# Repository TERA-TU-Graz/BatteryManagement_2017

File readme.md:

# Battery Management System (BMS) with use of STM32 CubeMX

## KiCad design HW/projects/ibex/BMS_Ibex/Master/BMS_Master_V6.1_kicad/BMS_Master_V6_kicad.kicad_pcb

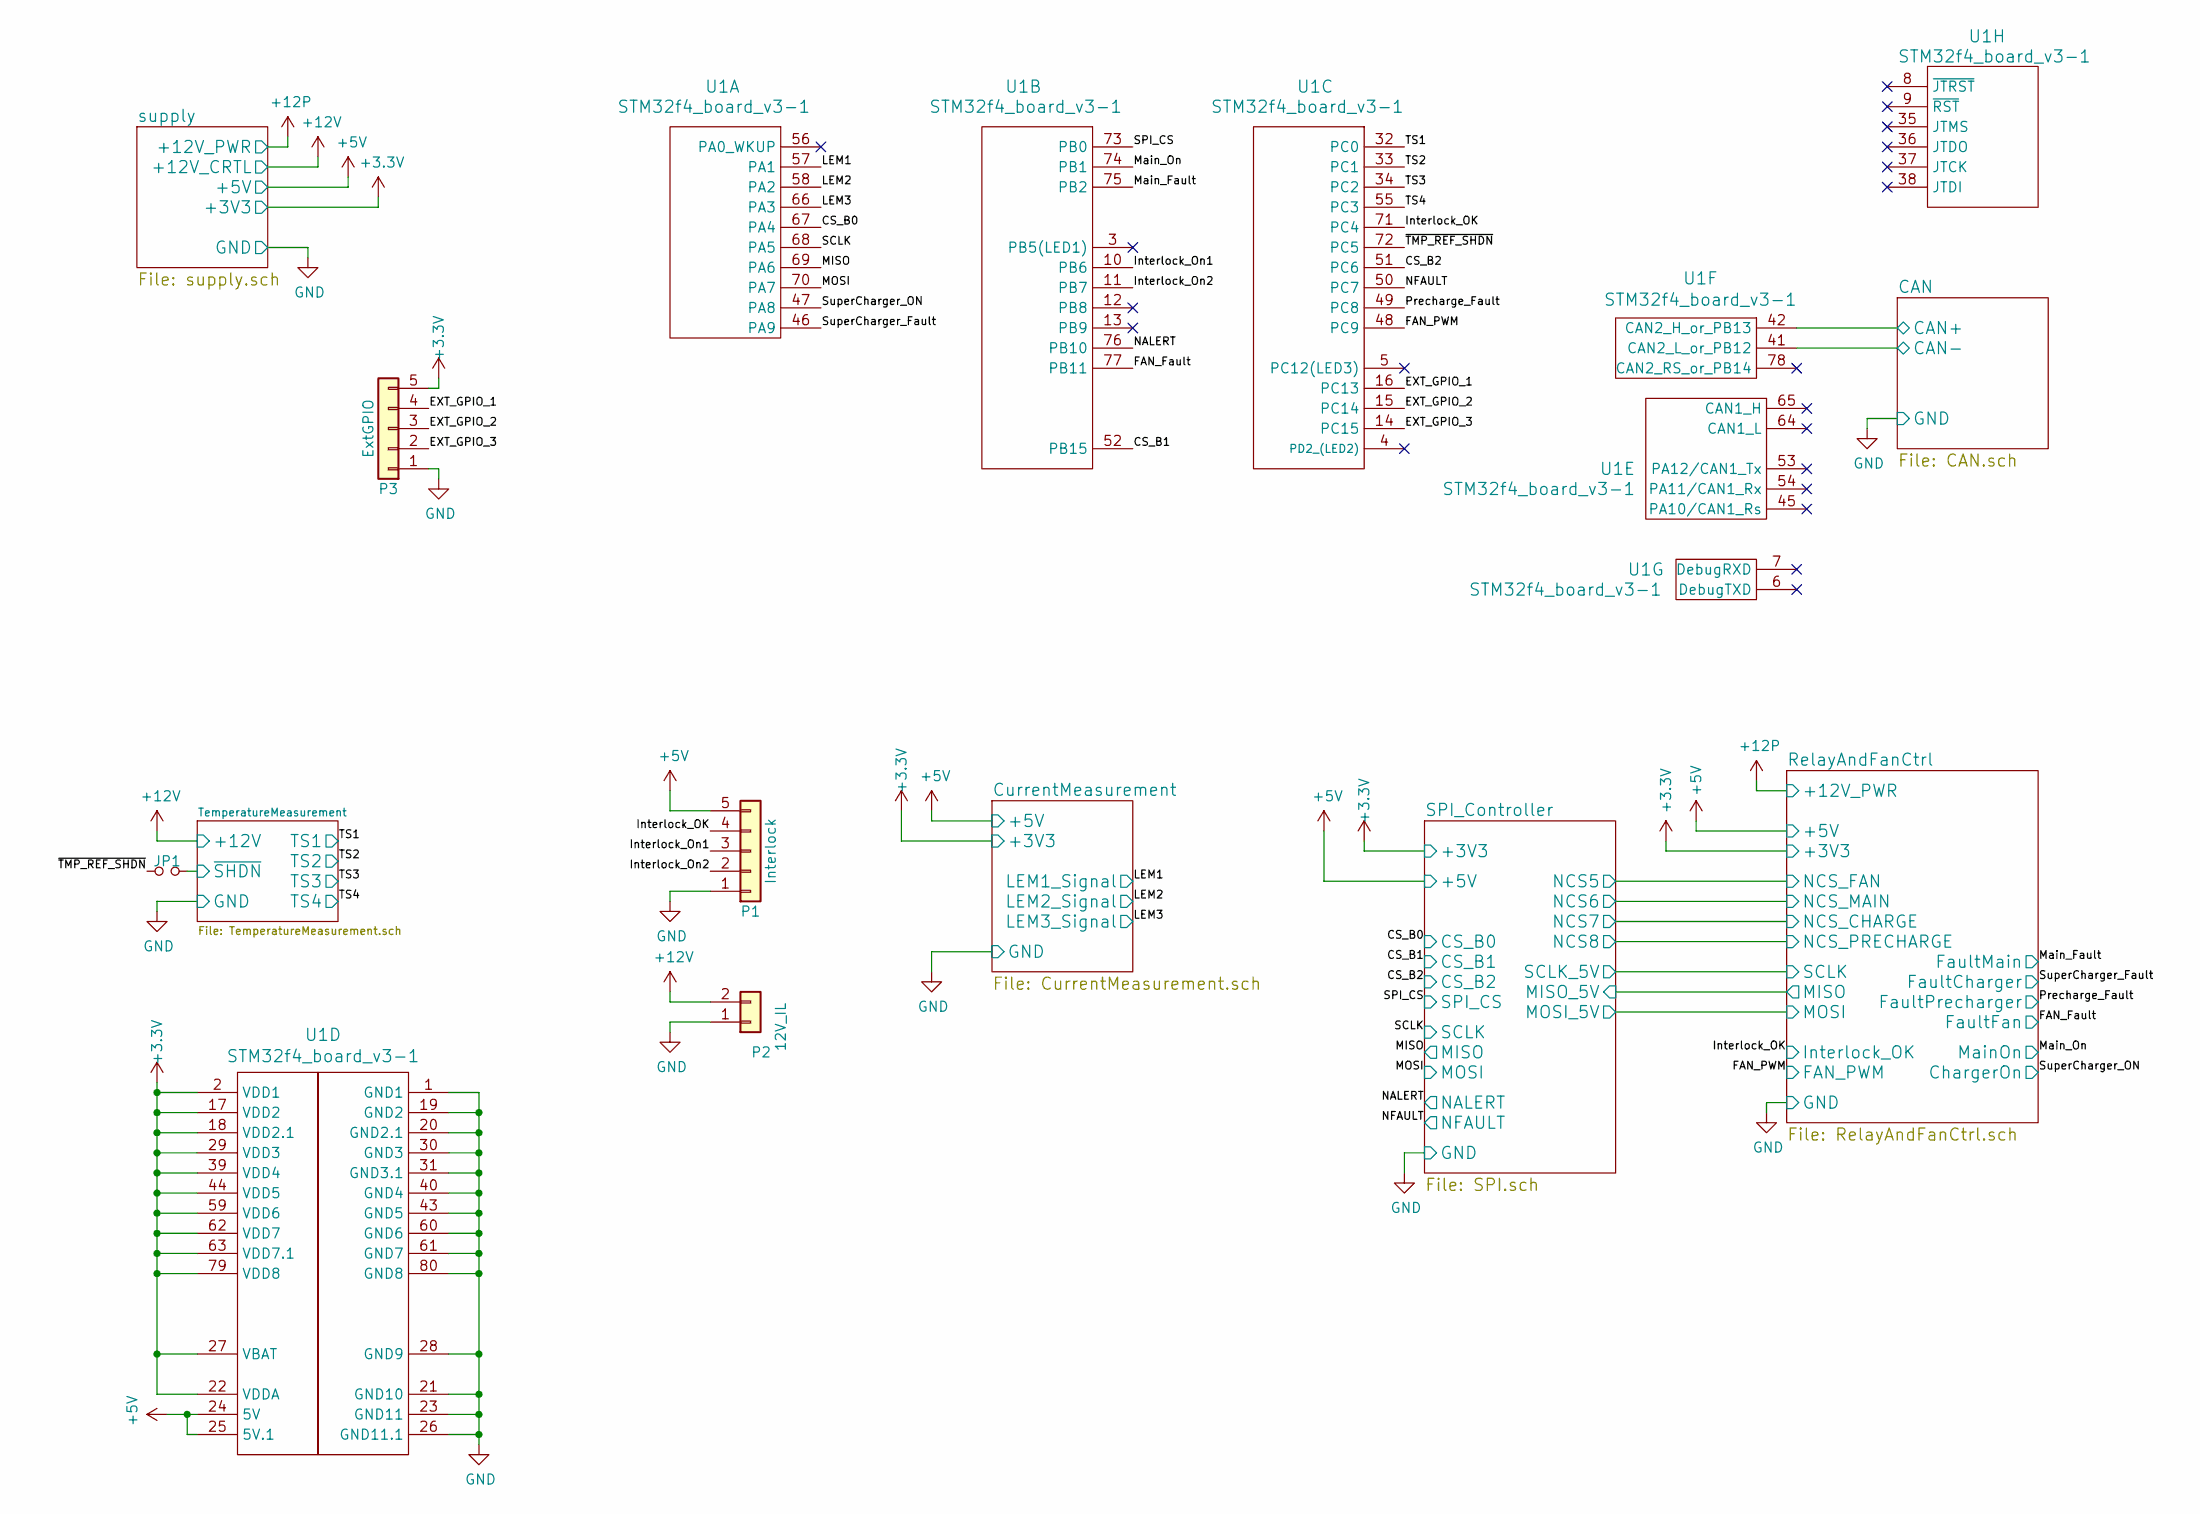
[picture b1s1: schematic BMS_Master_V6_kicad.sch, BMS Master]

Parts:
JP1: Jumper_NO_Small; SOLDERJUMPER_2
P1: Interlock; JST_XH_B05B-XH-A_05x2.50mm_Straight
P2: 12V_IL; JST_XH_B02B-XH-A_02x2.50mm_Straight
P3: ExtGPIO; JST_EH_B05B-EH-A_05x2.50mm_Straight
U1: STM32f4_board_v3-1; STM32f4-board_v3-1

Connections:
+3V3: P3.5, U1.2 (VDD1), U1.17 (VDD2), U1.18 (VDD2.1), U1.22 (VDDA), U1.27 (VBAT), U1.29 (VDD3), U1.39 (VDD4), U1.44 (VDD5), U1.59 (VDD6), U1.62 (VDD7), U1.63 (VDD7.1), U1.79 (VDD8); also elsewhere on the board
+5V: P1.5, U1.24 (5V), U1.25 (5V.1); also elsewhere on the board
+12V: P2.2; also elsewhere on the board
/CAN/CAN+: U1.42 (CAN2_H_or_PB13); also elsewhere on the board
/CAN/CAN-: U1.41 (CAN2_L_or_PB12); also elsewhere on the board
/CS_B0: U1.67 (PA4); also elsewhere on the board
/CS_B1: U1.52 (PB15); also elsewhere on the board
/CS_B2: U1.51 (PC6); also elsewhere on the board
/EXT_GPIO_1: P3.4, U1.16 (PC13)
/EXT_GPIO_2: P3.3, U1.15 (PC14)
/EXT_GPIO_3: P3.2, U1.14 (PC15)
/FAN_Fault: U1.77 (PB11); also elsewhere on the board
/FAN_PWM: U1.48 (PC9); also elsewhere on the board
/Interlock_OK: P1.4, U1.71 (PC4); also elsewhere on the board
/Interlock_On1: P1.3, U1.10 (PB6)
/Interlock_On2: P1.2, U1.11 (PB7)
/LEM1: U1.57 (PA1); also elsewhere on the board
/LEM2: U1.58 (PA2); also elsewhere on the board
/LEM3: U1.66 (PA3); also elsewhere on the board
/MISO: U1.69 (PA6); also elsewhere on the board
/MOSI: U1.70 (PA7); also elsewhere on the board
/Main_Fault: U1.75 (PB2); also elsewhere on the board
/Main_On: U1.74 (PB1); also elsewhere on the board
/NALERT: U1.76 (PB10); also elsewhere on the board
/NFAULT: U1.50 (PC7); also elsewhere on the board
/Precharge_Fault: U1.49 (PC8); also elsewhere on the board
/SCLK: U1.68 (PA5); also elsewhere on the board
/SPI_CS: U1.73 (PB0); also elsewhere on the board
/SuperCharger_Fault: U1.46 (PA9); also elsewhere on the board
/SuperCharger_ON: U1.47 (PA8); also elsewhere on the board
/TS1: U1.32 (PC0); also elsewhere on the board
/TS2: U1.33 (PC1); also elsewhere on the board
/TS3: U1.34 (PC2); also elsewhere on the board
/TS4: U1.55 (PC3); also elsewhere on the board
/TemperatureMeasurement/~SHDN: JP1.2; also elsewhere on the board
/~TMP_REF_SHDN: JP1.1, U1.72 (PC5)
GND: P1.1, P2.1, P3.1, U1.1 (GND1), U1.19 (GND2), U1.20 (GND2.1), U1.21 (GND10), U1.23 (GND11), U1.26 (GND11.1), U1.28 (GND9), U1.30 (GND3), U1.31 (GND3.1), U1.40 (GND4), U1.43 (GND5), U1.60 (GND6), U1.61 (GND7), U1.80 (GND8); also elsewhere on the board

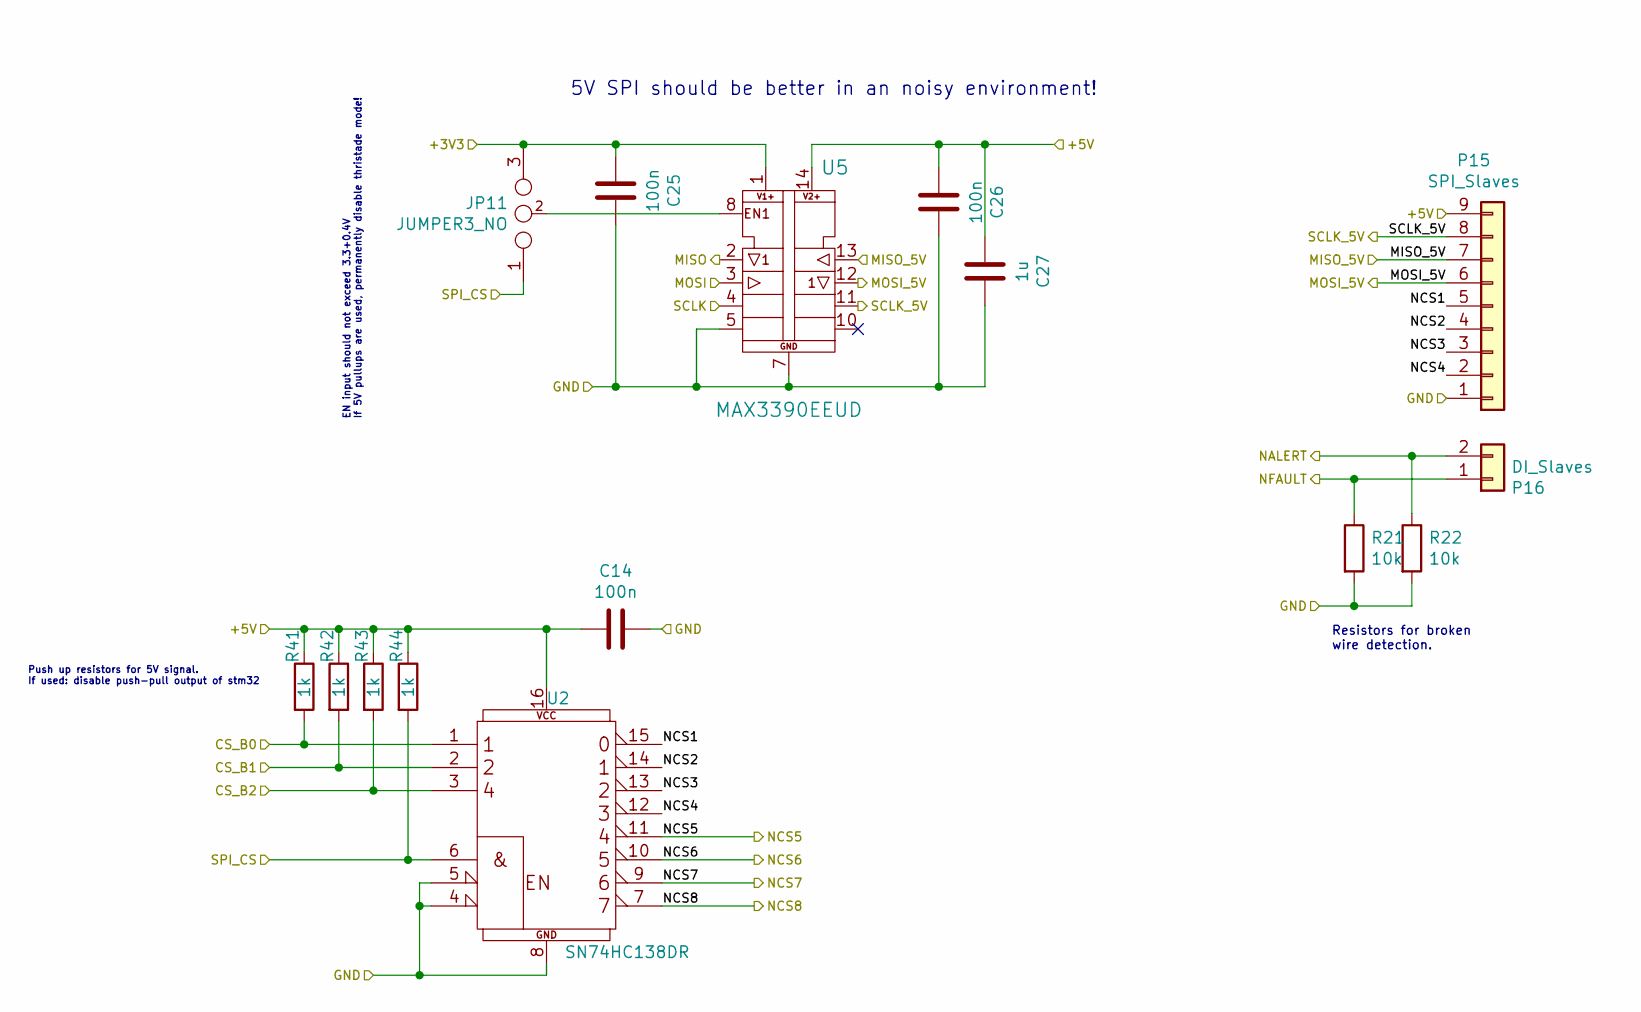
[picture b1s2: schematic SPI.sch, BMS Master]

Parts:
C14, C25, C26: 100n; C_0603in
C27: 1u; C_0805in
JP11: JUMPER3_NO; SOLDERJUMPER_3
P15: SPI_Slaves; Molex_PicoBlade_53398-0971_09x1.25mm_Straight
P16: DI_Slaves; JST_XH_B02B-XH-A_02x2.50mm_Straight
R21, R22: 10k; R_0805in
R41, R42, R43, R44: 1k; R_0805in
U2: SN74HC138DR
U5: MAX3390EEUD

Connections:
+3V3: C25.2, JP11.3, U5.1 (V1+); also elsewhere on the board
+5V: C14.2, C26.2, C27.2, P15.9, R41.1, R42.1, R43.1, R44.1, U2.16 (VCC), U5.14 (V2+); also elsewhere on the board
/CS_B0: R41.2, U2.1 (A1); also elsewhere on the board
/CS_B1: R42.2, U2.2 (A2); also elsewhere on the board
/CS_B2: R43.2, U2.3 (A4); also elsewhere on the board
/MISO: U5.2 (OUT1); also elsewhere on the board
/MOSI: U5.3 (IN2); also elsewhere on the board
/NALERT: P16.2, R22.1; also elsewhere on the board
/NFAULT: P16.1, R21.1; also elsewhere on the board
/RelayAndFanCtrl/MISO: P15.7, U5.13 (IN1); also elsewhere on the board
/RelayAndFanCtrl/MOSI: P15.6, U5.12 (OUT2); also elsewhere on the board
/RelayAndFanCtrl/SCLK: P15.8, U5.11 (OUT3); also elsewhere on the board
/SCLK: U5.4 (IN3); also elsewhere on the board
/SPI_CS: JP11.1 (m), R44.2, U2.6 (E3); also elsewhere on the board
/SPI_Controller/NCS1: P15.5, U2.15 (O0)
/SPI_Controller/NCS2: P15.4, U2.14 (O1)
/SPI_Controller/NCS3: P15.3, U2.13 (O2)
/SPI_Controller/NCS4: P15.2, U2.12 (O3)
/SPI_Controller/NCS5: U2.11 (O4); also elsewhere on the board
/SPI_Controller/NCS6: U2.10 (O5); also elsewhere on the board
/SPI_Controller/NCS7: U2.9 (O6); also elsewhere on the board
/SPI_Controller/NCS8: U2.7 (O7); also elsewhere on the board
GND: C14.1, C25.1, C26.1, C27.1, P15.1, R21.2, R22.2, U2.4 (E1), U2.5 (E2), U2.8 (GND), U5.5 (IN4), U5.7 (GND); also elsewhere on the board
unnamed: JP11.2, U5.8 (EN1)

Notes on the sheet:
Resistors for broken wire detection.
5V SPI should be better in an noisy environment!
EN input should not exceed 3.3+0.4V If 5V pullups are used, permanently disable thristade mode!
Push up resistors for 5V signal. If used: disable push-pull output of stm32

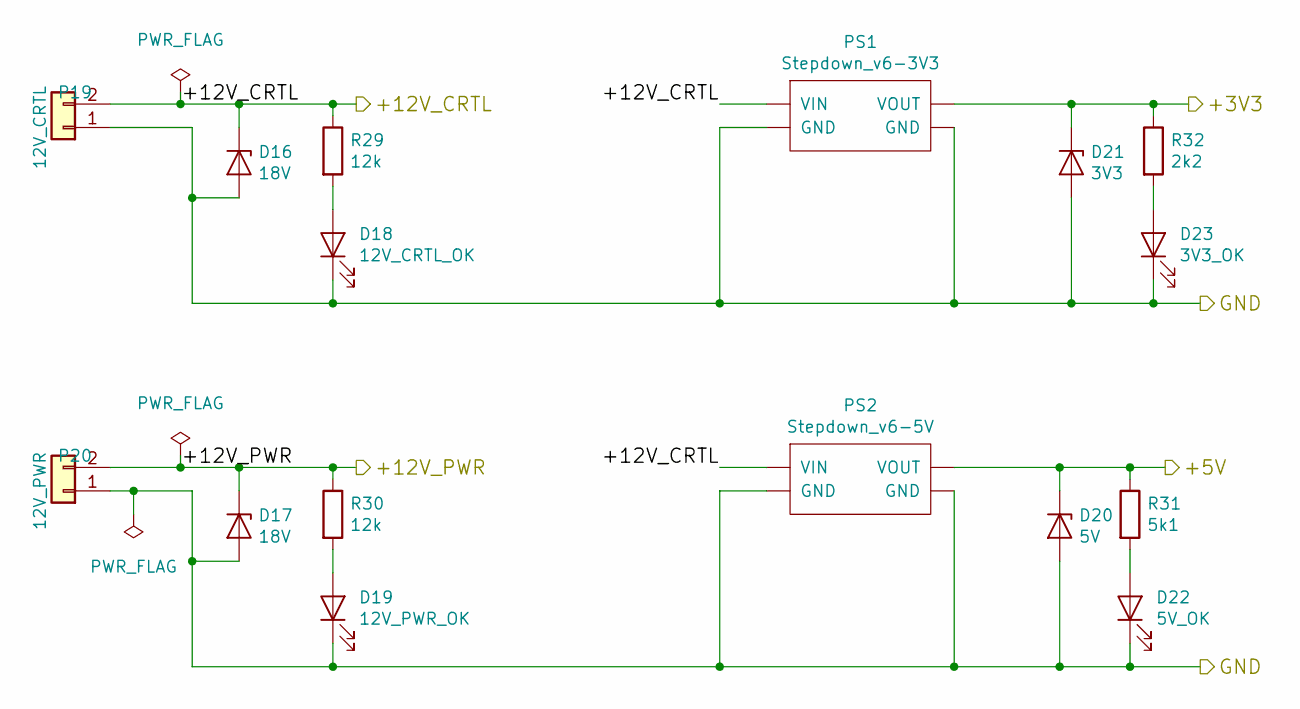
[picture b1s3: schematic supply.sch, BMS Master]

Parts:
D16, D17: 18V; DO-214AA_with_vias_in_pad
D18: 12V_CRTL_OK; LED_0805
D19: 12V_PWR_OK; LED_0805
D20: 5V; DO-216AA
D21: 3V3; DO-216AA
D22: 5V_OK; LED_0805
D23: 3V3_OK; LED_0805
P19: 12V_CRTL; JST_XH_B02B-XH-A_02x2.50mm_Straight
P20: 12V_PWR; MCV_1.5_2-GF-3.5
PS1: Stepdown_v6-3V3; DCDC_Stepdown_v6
PS2: Stepdown_v6-5V; DCDC_Stepdown_v6
R29, R30: 12k; R_0805in
R31: 5k1; R_0805in
R32: 2k2; R_0805in

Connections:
+3V3: D21.1 (K), PS1.2 (VOUT), R32.1; also elsewhere on the board
+5V: D20.1 (K), PS2.2 (VOUT), R31.1; also elsewhere on the board
+12P: D17.1 (K), P20.2, R30.1; also elsewhere on the board
+12V: D16.1 (K), P19.2, PS1.1 (VIN), PS2.1 (VIN), R29.1; also elsewhere on the board
GND: D16.2 (A), D17.2 (A), D18.1 (K), D19.1 (K), D20.2 (A), D21.2 (A), D22.1 (K), D23.1 (K), P19.1, P20.1, PS1.3 (GND), PS1.4 (GND), PS2.3 (GND), PS2.4 (GND); also elsewhere on the board
unnamed: D18.2 (A), R29.2
unnamed: D19.2 (A), R30.2
unnamed: D22.2 (A), R31.2
unnamed: D23.2 (A), R32.2

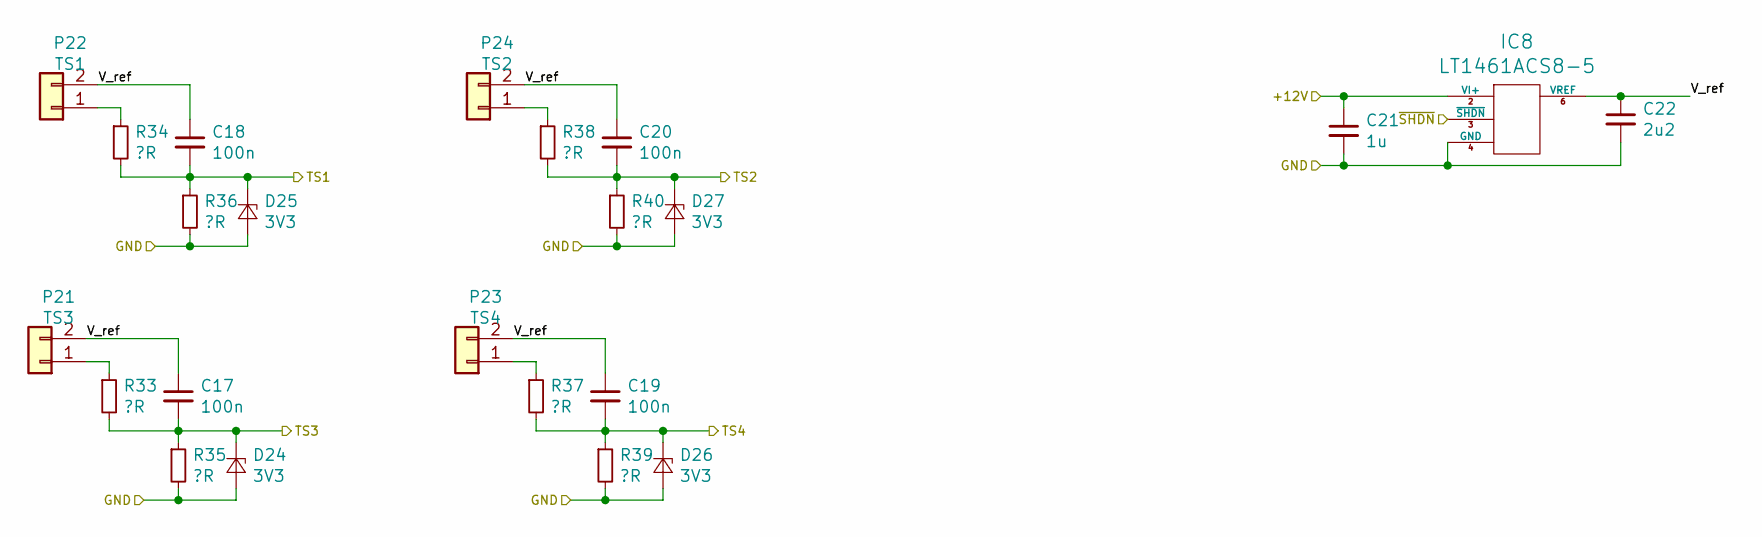
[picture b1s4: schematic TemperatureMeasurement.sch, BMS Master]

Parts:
C17, C18, C19, C20: 100n; C_0603in
C21: 1u; C_0805in
C22: 2u2; C_0805in
D24, D25, D26, D27: 3V3; DO-216AA
IC8: LT1461ACS8-5; LT1461ACS8
P21: TS3; Molex_PicoBlade_53398-0271_02x1.25mm_Straight
P22: TS1; Molex_PicoBlade_53398-0271_02x1.25mm_Straight
P23: TS4; Molex_PicoBlade_53398-0271_02x1.25mm_Straight
P24: TS2; Molex_PicoBlade_53398-0271_02x1.25mm_Straight
R33, R34, R35, R36, R37, R38, R39, R40: ?R; R_0603in

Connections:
+12V: C21.1, IC8.2 (VI+); also elsewhere on the board
/TS1: C18.2, D25.1 (K), R34.2, R36.1; also elsewhere on the board
/TS2: C20.2, D27.1 (K), R38.2, R40.1; also elsewhere on the board
/TS3: C17.2, D24.1 (K), R33.2, R35.1; also elsewhere on the board
/TS4: C19.2, D26.1 (K), R37.2, R39.1; also elsewhere on the board
/TemperatureMeasurement/V_ref: C17.1, C18.1, C19.1, C20.1, C22.1, IC8.6 (VREF), P21.2, P22.2, P23.2, P24.2
/TemperatureMeasurement/~SHDN: IC8.3 (~SHDN); also elsewhere on the board
GND: C21.2, C22.2, D24.2 (A), D25.2 (A), D26.2 (A), D27.2 (A), IC8.4 (GND), R35.2, R36.2, R39.2, R40.2; also elsewhere on the board
unnamed: P21.1, R33.1
unnamed: P22.1, R34.1
unnamed: P23.1, R37.1
unnamed: P24.1, R38.1

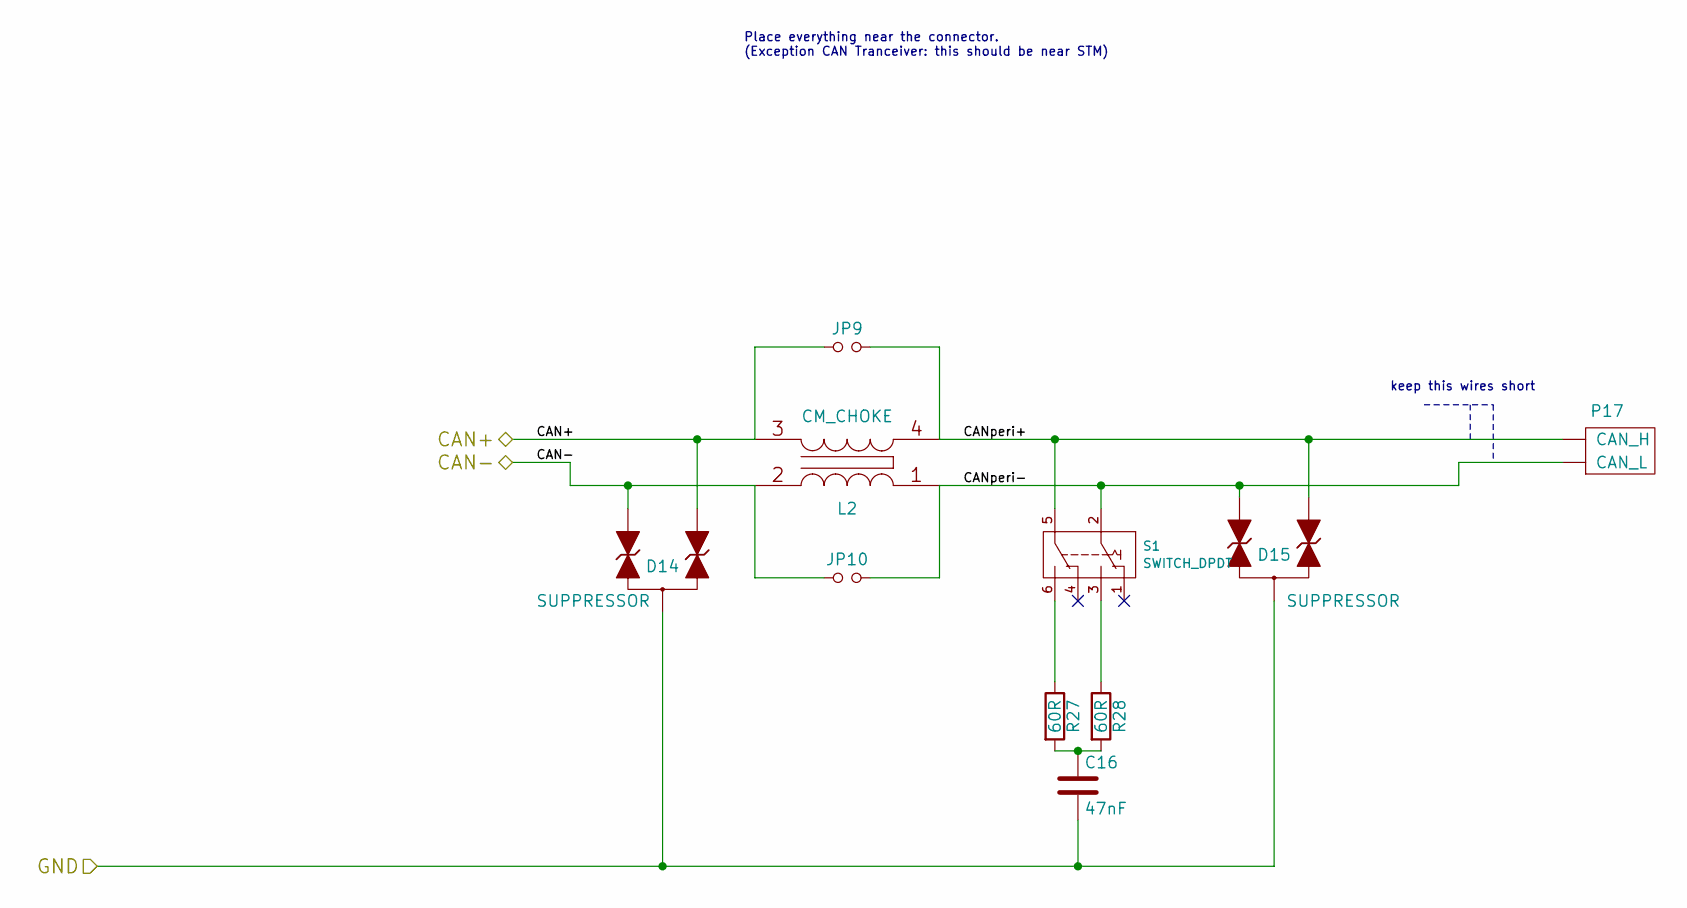
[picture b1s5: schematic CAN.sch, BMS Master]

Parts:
C15: 47nF; C_0603in
D12, D13: SUPPRESSOR; SOT-23
JP7, JP8: Jumper_NO_Small; SOLDERJUMPER_2
L1: CM_CHOKE; L_ACT45B-XXX-2P_common-mode-choke
P17: CAN_CON_2pol; JST_PH_B2B-PH-K_02x2.00mm_Straight
R24, R25: 60R; R_0603in
S1: SWITCH_DPDT; CuK_JS202011CQN_DPDT

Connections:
/CAN/CANperi+: P17.2 (CAN_H), S1.5; also elsewhere on the board
/CAN/CANperi-: P17.1 (CAN_L), S1.2; also elsewhere on the board
unnamed 93: S1.6; also elsewhere on the board
unnamed 94: S1.3; also elsewhere on the board

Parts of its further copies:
C16: 47nF; C_0603in
D14, D15: SUPPRESSOR; SOT-23
JP9, JP10: Jumper_NO_Small; SOLDERJUMPER_2
L2: CM_CHOKE; L_ACT45B-XXX-2P_common-mode-choke
R27, R28: 60R; R_0603in

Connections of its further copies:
/CAN/CAN+: D14.2 (Pin2), JP9.1, L2.3 (SA); also elsewhere on the board
/CAN/CAN-: D14.1 (Pin1), JP10.1, L2.2 (AB); also elsewhere on the board
/CAN/CANperi+: D15.2 (Pin2), JP9.2, L2.4 (SB); also elsewhere on the board
/CAN/CANperi-: D15.1 (Pin1), JP10.2, L2.1 (AA); also elsewhere on the board
GND: C16.2, D14.3 (Pin3), D15.3 (Pin3); also elsewhere on the board
unnamed: C16.1, R27.2, R28.2
unnamed 93: R27.1; also elsewhere on the board
unnamed 94: R28.1; also elsewhere on the board

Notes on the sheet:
Place everything near the connector. (Exception CAN Tranceiver: this should be near STM)
keep this wires short

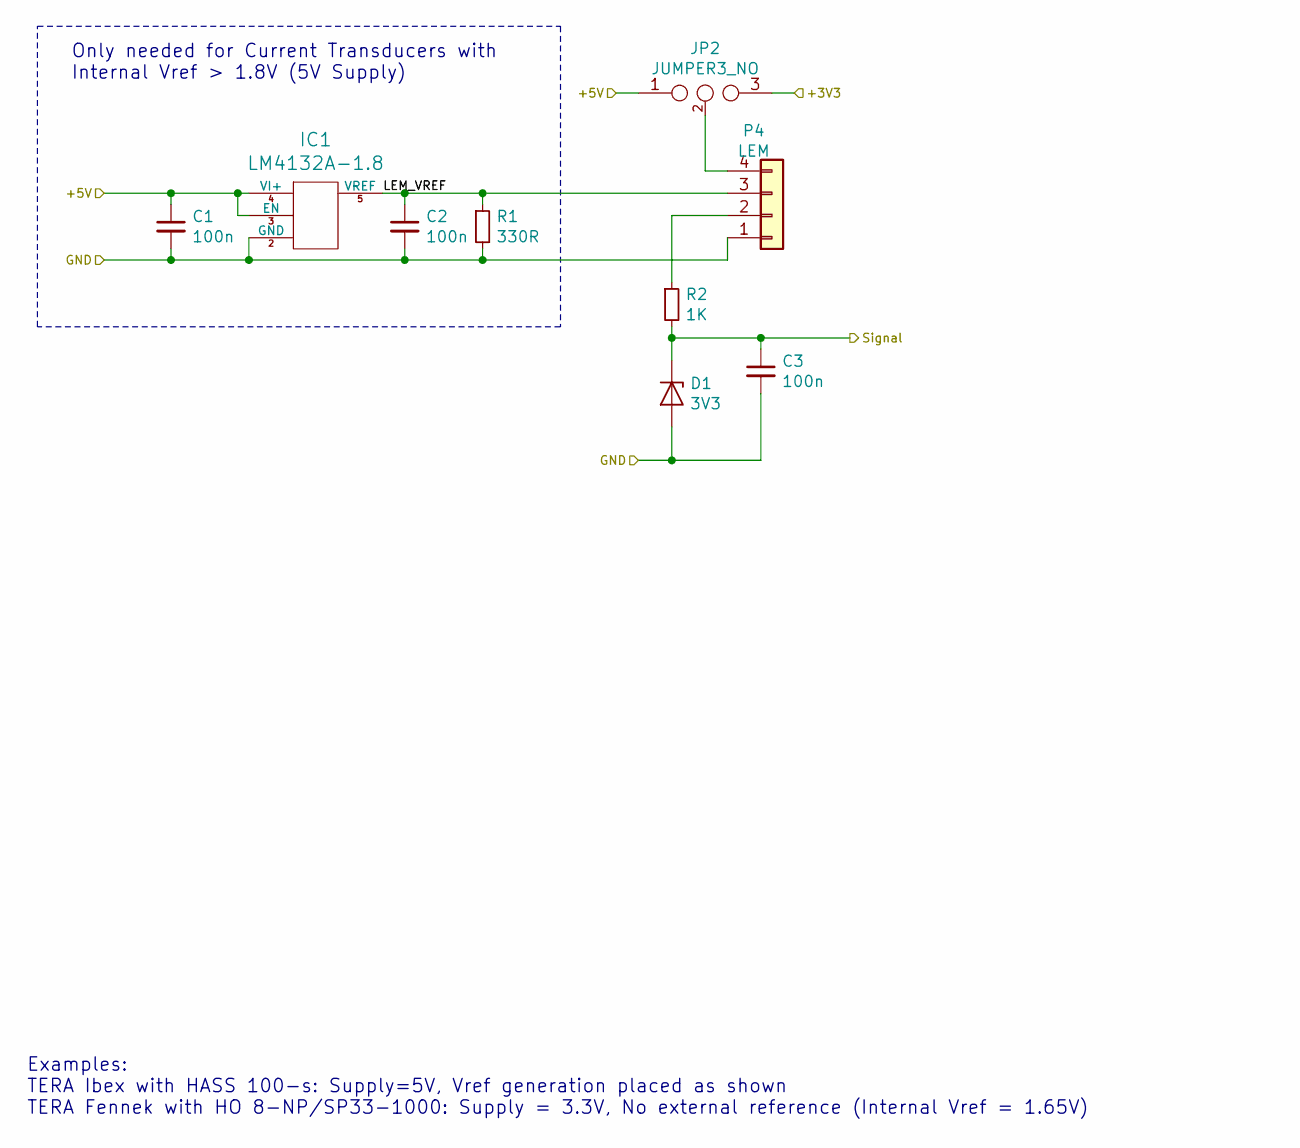
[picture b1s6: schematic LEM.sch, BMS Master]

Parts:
C1, C2, C3: 100n; C_0603in
D1: 3V3; DO-216AA
IC1: LM4132A-1.8; LM4132A
JP2: JUMPER3_NO; SOLDERJUMPER_3
P4: LEM; Molex_PicoBlade_53398-0471_04x1.25mm_Straight
R1: 330R; R_0603in
R2: 1K; R_0805in

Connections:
+3V3: JP2.3; also elsewhere on the board
+5V: C1.1, IC1.3 (EN), IC1.4 (VI+), JP2.1 (m); also elsewhere on the board
/CurrentMeasurement/LEM1/LEM_VREF: C2.1, IC1.5 (VREF), P4.3, R1.1
/LEM1: C3.1, D1.1 (K), R2.2; also elsewhere on the board
GND: C1.2, C2.2, C3.2, D1.2 (A), IC1.2 (GND), P4.1, R1.2; also elsewhere on the board
unnamed: JP2.2, P4.4
unnamed: P4.2, R2.1

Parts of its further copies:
C4, C5, C6, C7, C8, C9: 100n; C_0603in
D2, D3: 3V3; DO-216AA
IC2, IC3: LM4132A-1.8; LM4132A
JP3, JP4: JUMPER3_NO; SOLDERJUMPER_3
P5, P6: LEM; Molex_PicoBlade_53398-0471_04x1.25mm_Straight
R3, R5: 330R; R_0603in
R4, R6: 1K; R_0805in

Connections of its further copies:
+3V3: JP3.3, JP4.3; also elsewhere on the board
+5V: C4.1, C7.1, IC2.3 (EN), IC2.4 (VI+), IC3.3 (EN), IC3.4 (VI+), JP3.1 (m), JP4.1 (m); also elsewhere on the board
/CurrentMeasurement/LEM2/LEM_VREF: C5.1, IC2.5 (VREF), P5.3, R3.1
/CurrentMeasurement/LEM3/LEM_VREF: C8.1, IC3.5 (VREF), P6.3, R5.1
/LEM2: C6.1, D2.1 (K), R4.2; also elsewhere on the board
/LEM3: C9.1, D3.1 (K), R6.2; also elsewhere on the board
GND: C4.2, C5.2, C6.2, C7.2, C8.2, C9.2, D2.2 (A), D3.2 (A), IC2.2 (GND), IC3.2 (GND), P5.1, P6.1, R3.2, R5.2; also elsewhere on the board
unnamed: JP3.2, P5.4
unnamed: JP4.2, P6.4
unnamed: P5.2, R4.1
unnamed: P6.2, R6.1

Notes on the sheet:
Only needed for Current Transducers with Internal Vref > 1.8V (5V Supply)
Examples: TERA Ibex with HASS 100-s: Supply=5V, Vref generation placed as shown TERA Fennek with HO 8-NP/SP33-1000: Supply = 3.3V, No external reference (Internal Vref = 1.65V)

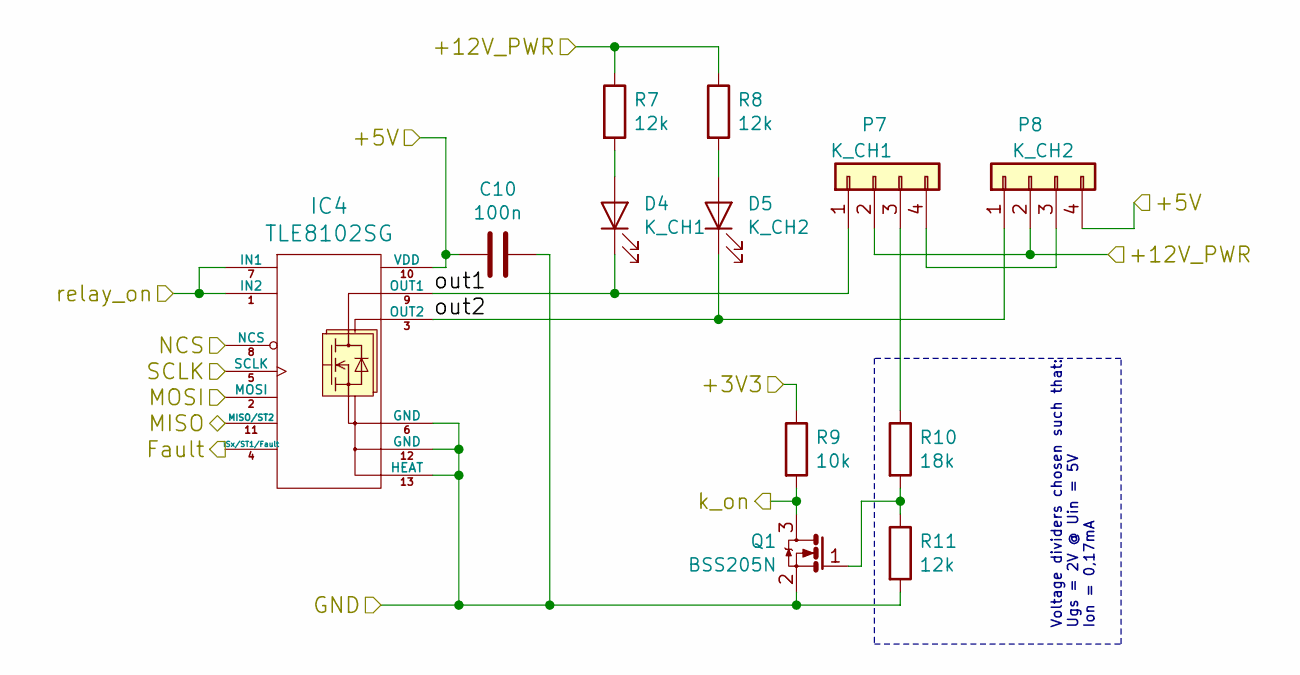
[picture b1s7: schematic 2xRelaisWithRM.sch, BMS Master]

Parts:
C10: 100n; C_0603in
D4: K_CH1; LED_0805
D5: K_CH2; LED_0805
IC4: TLE8102SG; INF-PG-DSO-12-11-EP_N_EPvias
P7: K_CH1; JST_XH_B04B-XH-A_04x2.50mm_Straight
P8: K_CH2; JST_XH_B04B-XH-A_04x2.50mm_Straight
Q1: BSS205N; SOT-23
R7, R8, R11: 12k; R_0805in
R9: 10k; R_0603in
R10: 18k; R_0805in

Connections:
+3V3: R9.1; also elsewhere on the board
+5V: C10.2, IC4.10 (VDD), P8.4; also elsewhere on the board
+12P: P7.2, P8.2, R7.1, R8.1; also elsewhere on the board
/Interlock_OK: IC4.1 (IN2), IC4.7 (IN1); also elsewhere on the board
/RelayAndFanCtrl/MISO: IC4.11 (MISO/ST2); also elsewhere on the board
/RelayAndFanCtrl/MOSI: IC4.2 (MOSI); also elsewhere on the board
/RelayAndFanCtrl/SCLK: IC4.5 (SCLK); also elsewhere on the board
/RelayAndFanCtrl/SuperChargerRelais/out1: D4.1 (K), IC4.9 (OUT1), P7.1
/RelayAndFanCtrl/SuperChargerRelais/out2: D5.1 (K), IC4.3 (OUT2), P8.1
/SPI_Controller/NCS7: IC4.8 (NCS); also elsewhere on the board
/SuperCharger_Fault: IC4.4 (ISx/ST1/Fault); also elsewhere on the board
/SuperCharger_ON: Q1.3 (D), R9.2; also elsewhere on the board
GND: C10.1, IC4.6 (GND), IC4.12 (GND), IC4.13 (HEAT), Q1.2 (S), R11.2; also elsewhere on the board
unnamed: D4.2 (A), R7.2
unnamed: D5.2 (A), R8.2
unnamed: P7.3, R10.1
unnamed: P7.4, P8.3
unnamed: Q1.1 (G), R10.2, R11.1

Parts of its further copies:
C11: 100n; C_0603in
D6: K_CH1; LED_0805
D7: K_CH2; LED_0805
IC5: TLE8102SG; INF-PG-DSO-12-11-EP_N_EPvias
P9: K_CH1; JST_XH_B04B-XH-A_04x2.50mm_Straight
P10: K_CH2; JST_XH_B04B-XH-A_04x2.50mm_Straight
Q2: BSS205N; SOT-23
R12, R13, R16: 12k; R_0805in
R14: 10k; R_0603in
R15: 18k; R_0805in

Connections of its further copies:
+3V3: R14.1; also elsewhere on the board
+5V: C11.2, IC5.10 (VDD), P10.4; also elsewhere on the board
+12P: P9.2, P10.2, R12.1, R13.1; also elsewhere on the board
/Interlock_OK: IC5.1 (IN2), IC5.7 (IN1); also elsewhere on the board
/Main_Fault: IC5.4 (ISx/ST1/Fault); also elsewhere on the board
/Main_On: Q2.3 (D), R14.2; also elsewhere on the board
/RelayAndFanCtrl/MISO: IC5.11 (MISO/ST2); also elsewhere on the board
/RelayAndFanCtrl/MOSI: IC5.2 (MOSI); also elsewhere on the board
/RelayAndFanCtrl/MainRelais/out1: D6.1 (K), IC5.9 (OUT1), P9.1
/RelayAndFanCtrl/MainRelais/out2: D7.1 (K), IC5.3 (OUT2), P10.1
/RelayAndFanCtrl/SCLK: IC5.5 (SCLK); also elsewhere on the board
/SPI_Controller/NCS6: IC5.8 (NCS); also elsewhere on the board
GND: C11.1, IC5.6 (GND), IC5.12 (GND), IC5.13 (HEAT), Q2.2 (S), R16.2; also elsewhere on the board
unnamed: D6.2 (A), R12.2
unnamed: D7.2 (A), R13.2
unnamed: P9.3, R15.1
unnamed: P9.4, P10.3
unnamed: Q2.1 (G), R15.2, R16.1

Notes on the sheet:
Voltage dividers chosen such that: Ugs = 2V @ Uin = 5V Ion = 0,17mA

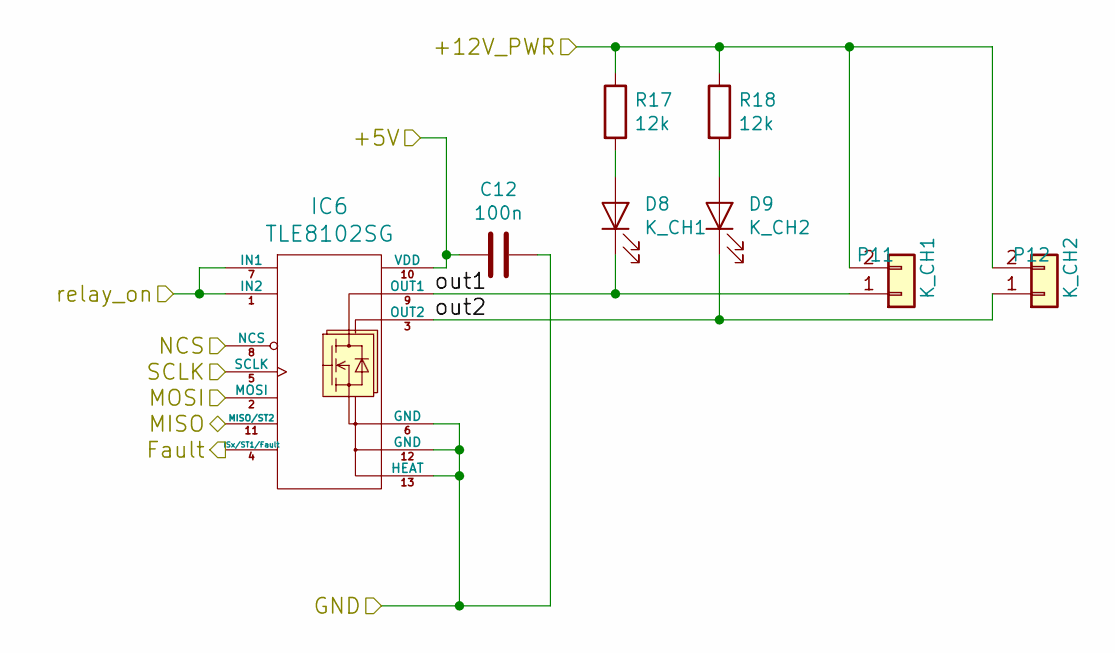
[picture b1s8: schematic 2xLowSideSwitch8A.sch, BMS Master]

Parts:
C12: 100n; C_0603in
D8: K_CH1; LED_0805
D9: K_CH2; LED_0805
IC6: TLE8102SG; INF-PG-DSO-12-11-EP_N_EPvias
P11: K_CH1; JST_XH_B02B-XH-A_02x2.50mm_Straight
P12: K_CH2; JST_XH_B02B-XH-A_02x2.50mm_Straight
R17, R18: 12k; R_0805in

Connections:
+5V: C12.2, IC6.10 (VDD); also elsewhere on the board
+12P: P11.2, P12.2, R17.1, R18.1; also elsewhere on the board
/Interlock_OK: IC6.1 (IN2), IC6.7 (IN1); also elsewhere on the board
/Precharge_Fault: IC6.4 (ISx/ST1/Fault); also elsewhere on the board
/RelayAndFanCtrl/MISO: IC6.11 (MISO/ST2); also elsewhere on the board
/RelayAndFanCtrl/MOSI: IC6.2 (MOSI); also elsewhere on the board
/RelayAndFanCtrl/PRECHARGER/out1: D8.1 (K), IC6.9 (OUT1), P11.1
/RelayAndFanCtrl/PRECHARGER/out2: D9.1 (K), IC6.3 (OUT2), P12.1
/RelayAndFanCtrl/SCLK: IC6.5 (SCLK); also elsewhere on the board
/SPI_Controller/NCS8: IC6.8 (NCS); also elsewhere on the board
GND: C12.1, IC6.6 (GND), IC6.12 (GND), IC6.13 (HEAT); also elsewhere on the board
unnamed: D8.2 (A), R17.2
unnamed: D9.2 (A), R18.2

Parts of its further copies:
C13: 100n; C_0603in
D10: K_CH1; LED_0805
D11: K_CH2; LED_0805
IC7: TLE8102SG; INF-PG-DSO-12-11-EP_N_EPvias
P13: K_CH1; JST_XH_B02B-XH-A_02x2.50mm_Straight
P14: K_CH2; JST_XH_B02B-XH-A_02x2.50mm_Straight
R19, R20: 12k; R_0805in

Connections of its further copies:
+5V: C13.2, IC7.10 (VDD); also elsewhere on the board
+12P: P13.2, P14.2, R19.1, R20.1; also elsewhere on the board
/FAN_Fault: IC7.4 (ISx/ST1/Fault); also elsewhere on the board
/FAN_PWM: IC7.1 (IN2), IC7.7 (IN1); also elsewhere on the board
/RelayAndFanCtrl/FANS/out1: D10.1 (K), IC7.9 (OUT1), P13.1
/RelayAndFanCtrl/FANS/out2: D11.1 (K), IC7.3 (OUT2), P14.1
/RelayAndFanCtrl/MISO: IC7.11 (MISO/ST2); also elsewhere on the board
/RelayAndFanCtrl/MOSI: IC7.2 (MOSI); also elsewhere on the board
/RelayAndFanCtrl/SCLK: IC7.5 (SCLK); also elsewhere on the board
/SPI_Controller/NCS5: IC7.8 (NCS); also elsewhere on the board
GND: C13.1, IC7.6 (GND), IC7.12 (GND), IC7.13 (HEAT); also elsewhere on the board
unnamed: D10.2 (A), R19.2
unnamed: D11.2 (A), R20.2

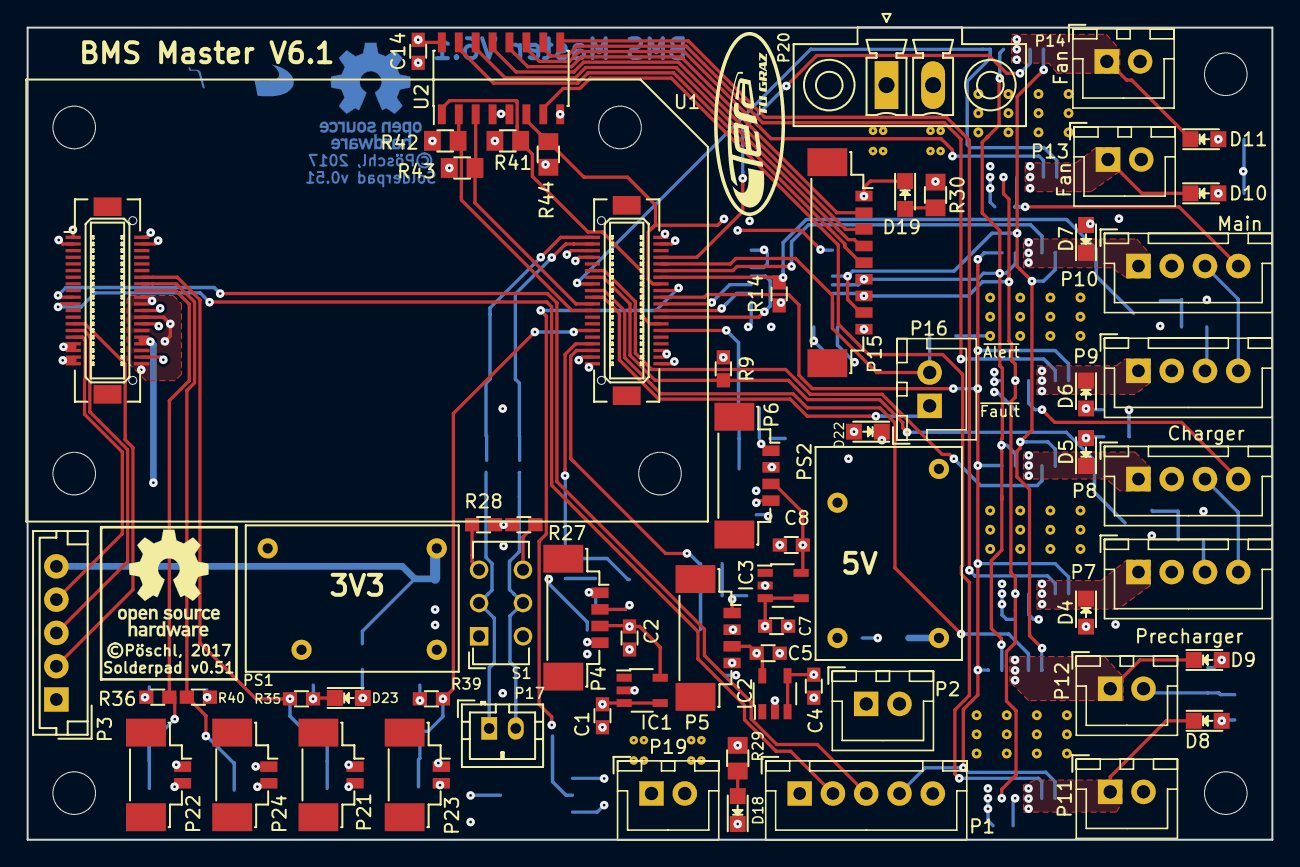
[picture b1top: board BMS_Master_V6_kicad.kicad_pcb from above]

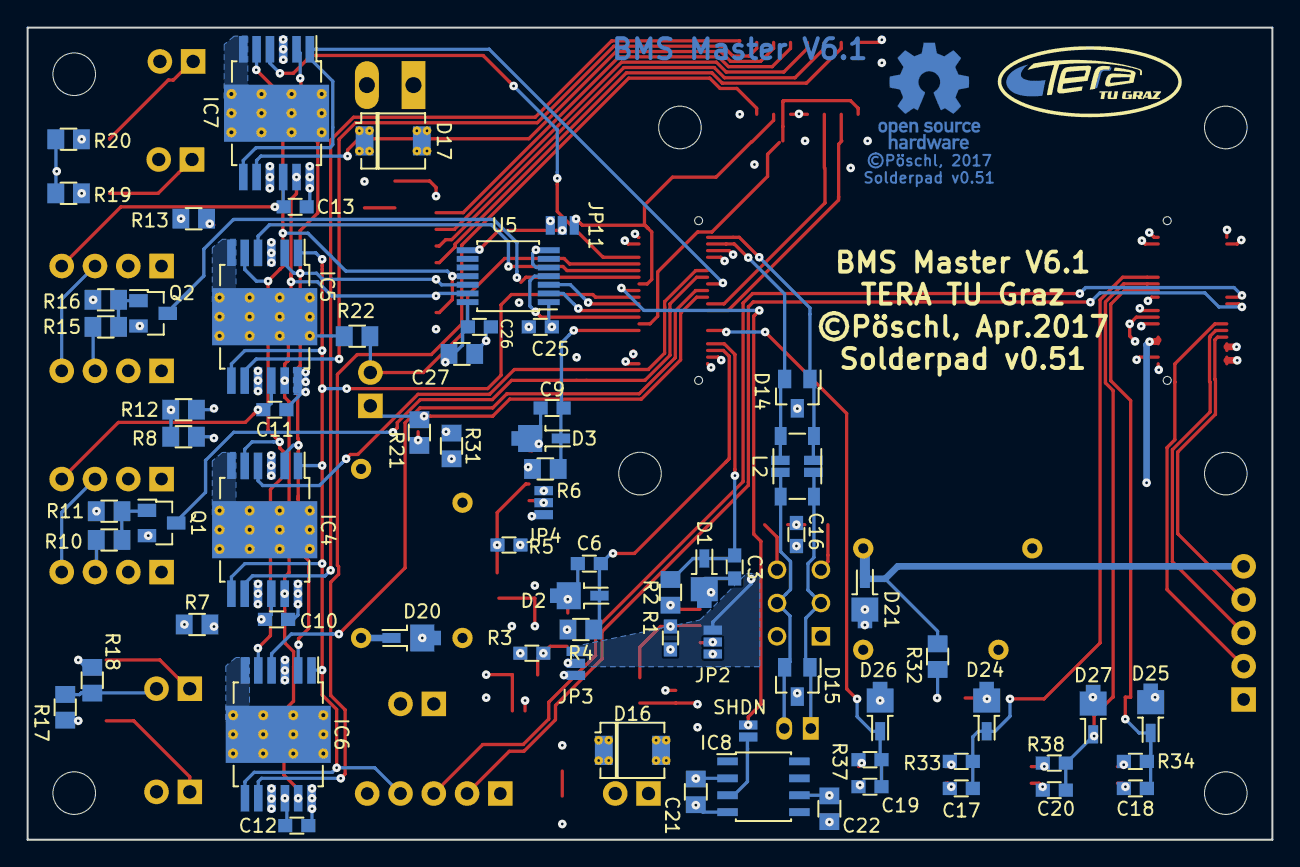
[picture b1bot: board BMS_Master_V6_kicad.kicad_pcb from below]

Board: 4 copper layers, 93.5 x 61.0 mm, 138 parts (73 on the bottom side), 95 nets.

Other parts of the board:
svg2mod: G***; TERA_Logo_SilkS_5x12.5mm
svg2mod#2: G***; TERA_Logo_SilkS_and_Cu_5x12.5mm

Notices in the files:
HW/projects/ibex/BMS_Ibex/Bus_Isolator/Bus_Isolator_V3.2/Bus_Isolator_V3-2.kicad_pcb:
©Pöschl, 2017
HW/projects/ibex/BMS_Ibex/HostInterfaceSplitter/HostInterfaceSplitter-V2.1/HostInterfaceSplitter-V2.kicad_pcb:
©2018 Pöschl
©Pöschl Rene, Apr. 2018
HW/projects/ibex/BMS_Ibex/HostInterfaceSplitter/HostInterfaceSplitter-V2/HostInterfaceSplitter-V2.kicad_pcb:
©2017 Pöschl
©Pöschl Rene, Jan. 2017
HW/projects/ibex/BMS_Ibex/Master/BMS_Master_V6.1_kicad/BMS_Master_V6_kicad.kicad_pcb:
©Pöschl, Apr.2017
HW/projects/ibex/BMS_Ibex/Messboard/bms_board_V5.1/bms_board.kicad_pcb:
©Pöachl, Jun. 2017
